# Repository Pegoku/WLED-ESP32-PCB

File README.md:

# WLED-PCB

This project is a WLED Controller designed using KiCad. The WLED-PCB is controlled using an ESP32 and can be powered via the Screw Terminals. It is capable of driving multiple RGB Strips and Neopixels. It also has a Fuse Holder per channel to protect the circuit from overcurrent.

## Schematic

## PCB Layout

## 3D View

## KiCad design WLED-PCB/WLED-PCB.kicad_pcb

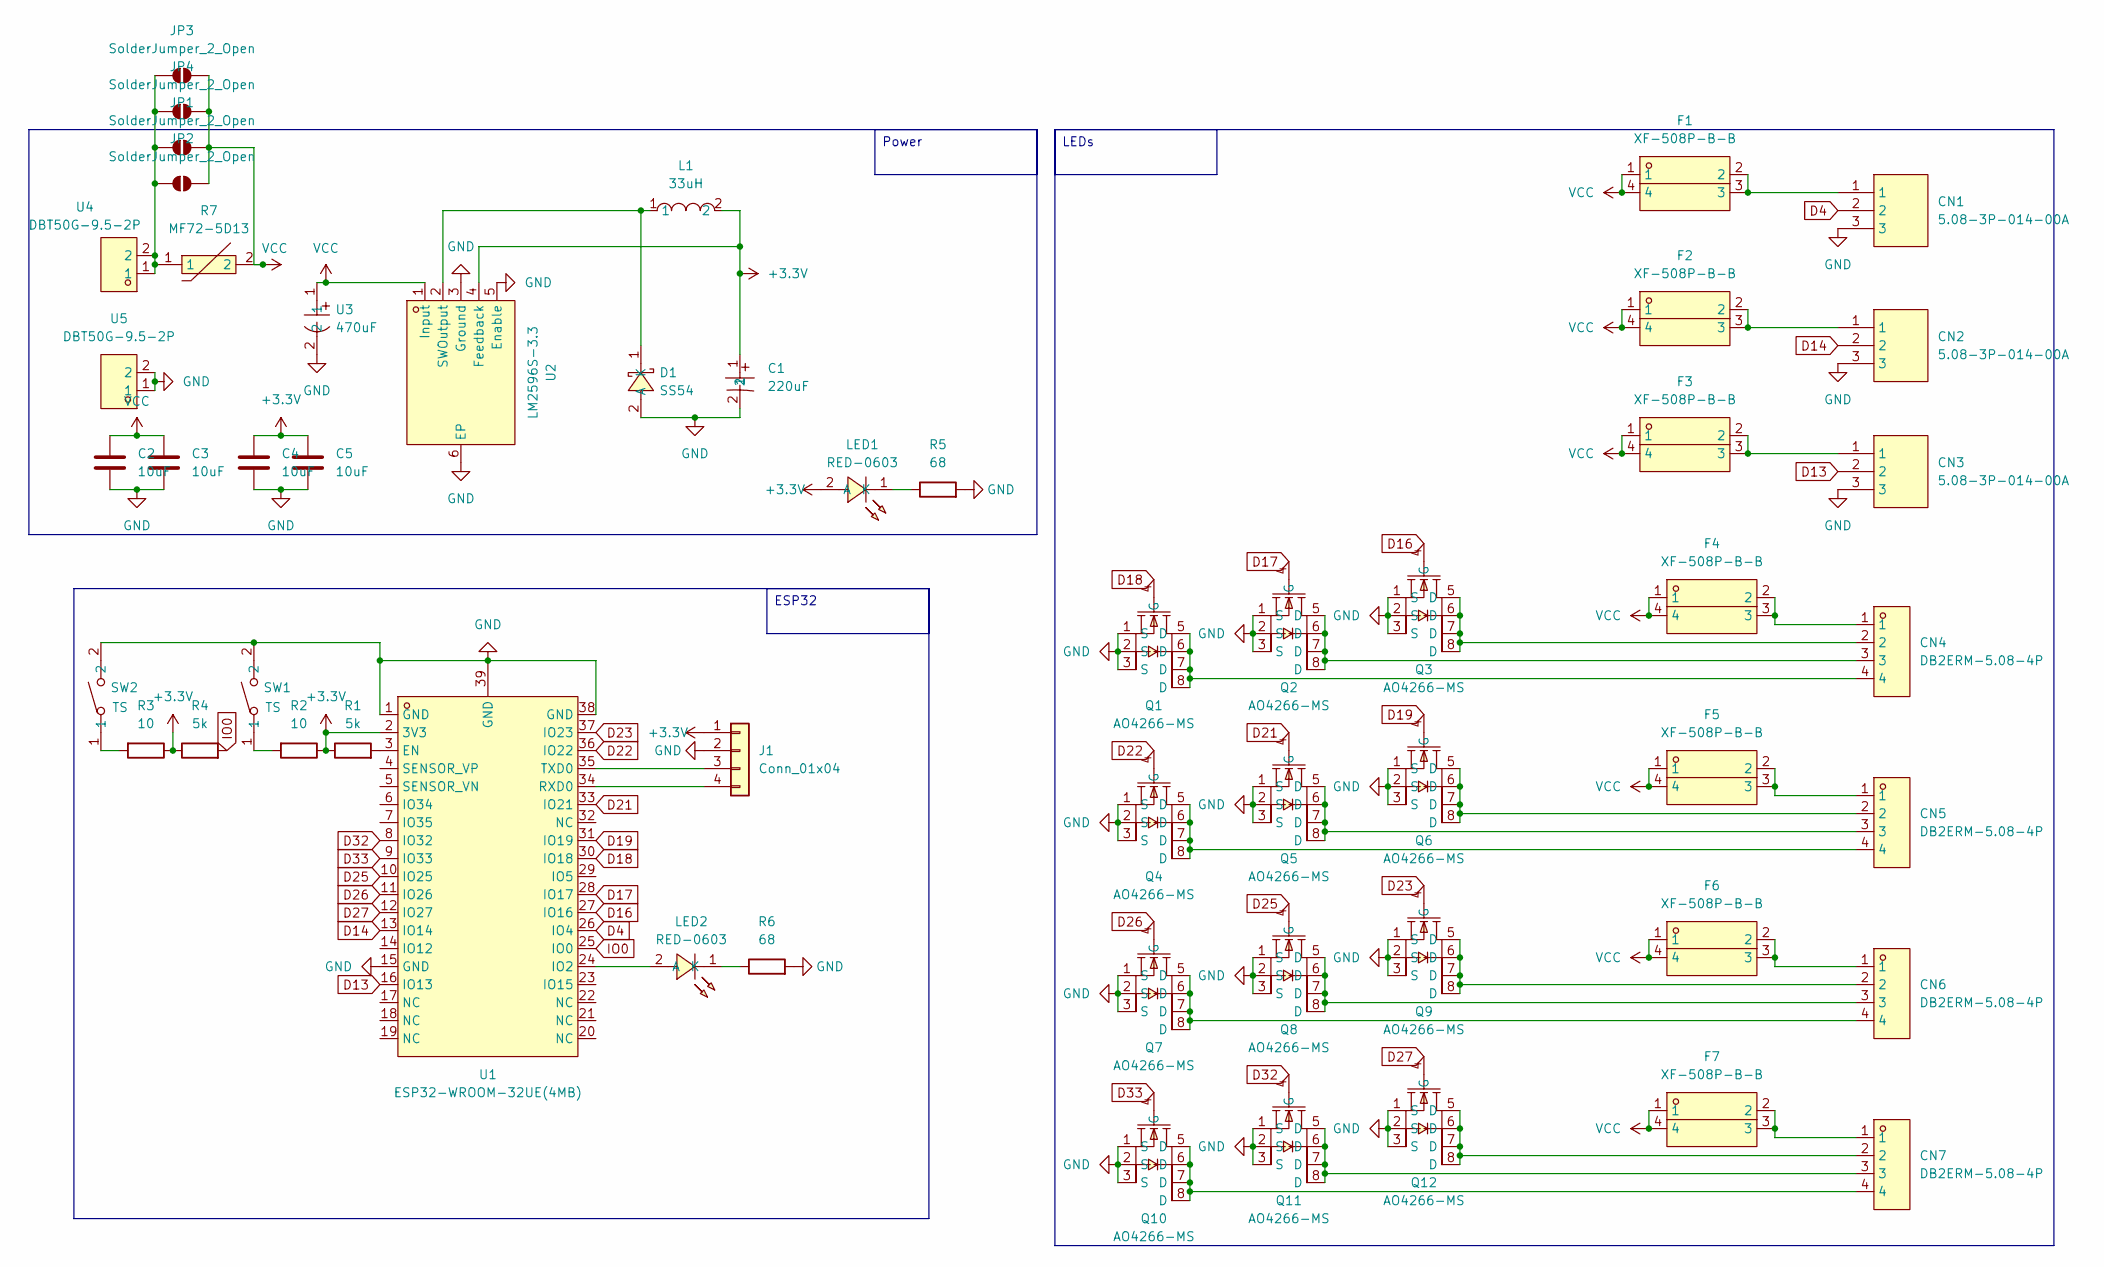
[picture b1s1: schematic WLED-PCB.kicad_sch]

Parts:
C1: 220uF; CAP-TH_BD6.3-P2.50-D1.0-FD; LCSC Part C122241
C2, C3, C4, C5: 10uF; C_1206_3216Metric_Pad1.33x1.80mm_HandSolder; LCSC C237304
CN1, CN2, CN3: 5.08-3P-014-00A; CONN-TH_WJ2EDGRM-5.08-3P; LCSC Part C49238
CN4, CN5, CN6, CN7: DB2ERM-5.08-4P; CONN-TH_4P-P5.08_DB2ERM-5.08-4P; LCSC Part C395755
D1: SS54; SMA_L4.3-W2.6-LS5.0-RD; LCSC Part C3018536
F1, F2, F3, F4, F5, F6, F7: XF-508P-B-B; FUSE-TH_4P-L16.0-W6.7; LCSC Part C19727305
J1: Conn_01x04; PinHeader_1x04_P2.54mm_Vertical
JP1, JP2, JP3, JP4: SolderJumper_2_Open; SolderJumper-2_P1.3mm_Open_TrianglePad1.0x1.5mm
L1: 33uH; IND-SMD_L7.1-W6.6_SRP6030VA; LCSC Part C22463826
LED1, LED2: RED-0603; LED0603-RD_RED; LCSC Part C965799
Q1, Q2, Q3, Q4, Q5, Q6, Q7, Q8, Q9, Q10, Q11, Q12: AO4266-MS; SOP-8_L4.9-W3.9-P1.27-LS6.0-BL; LCSC Part C3008148
R1, R4: 5k; R_0603_1608Metric_Pad0.98x0.95mm_HandSolder
R2, R3: 10; R_0603_1608Metric_Pad0.98x0.95mm_HandSolder
R5, R6: 68; R_0603_1608Metric_Pad0.98x0.95mm_HandSolder; LCSC C242566
R7: MF72-5D13; RES-TH_L15.5-W6.0-P7.50-D0.8-S5.20; LCSC Part C72683
SW1, SW2: TS; SW-SMD_L3.9-W3.0-P4.45; LCSC Part C720477
U1: ESP32-WROOM-32UE(4MB); WIFI-SMD_ESP32-WROOM-32UE; LCSC Part C701344
U2: LM2596S-3.3; TO-263-5_L10.0-W9.0-P1.70-LS15.2-BR; LCSC Part C7419978
U3: 470uF; CAP-TH_BD10.0-P5.00-D0.6-FD; LCSC Part C5438877
U4, U5: DBT50G-9.5-2P; CONN-TH_2P-P9.50_DBT50G-9.5-2P; LCSC Part C395958

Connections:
+3.3V: C1.1, C4.1, C5.1, J1.1, L1.2, LED1.2 (A), R1.1, R2.1, R3.1, R4.1, U1.2 (3V3), U2.4 (Feedback)
D4: CN1.2, U1.26 (IO4)
D13: CN3.2, U1.16 (IO13)
D14: CN2.2, U1.13 (IO14)
D16: Q3.4 (G), U1.27 (IO16)
D17: Q2.4 (G), U1.28 (IO17)
D18: Q1.4 (G), U1.30 (IO18)
D19: Q6.4 (G), U1.31 (IO19)
D21: Q5.4 (G), U1.33 (IO21)
D22: Q4.4 (G), U1.36 (IO22)
D23: Q9.4 (G), U1.37 (IO23)
D25: Q8.4 (G), U1.10 (IO25)
D26: Q7.4 (G), U1.11 (IO26)
D27: Q12.4 (G), U1.12 (IO27)
D32: Q11.4 (G), U1.8 (IO32)
D33: Q10.4 (G), U1.9 (IO33)
GND: C1.2, C2.2, C3.2, C4.2, C5.2, CN1.3, CN2.3, CN3.3, D1.2 (A), J1.2, Q1.1 (S), Q1.2 (S), Q1.3 (S), Q2.1 (S), Q2.2 (S), Q2.3 (S), Q3.1 (S), Q3.2 (S), Q3.3 (S), Q4.1 (S), Q4.2 (S), Q4.3 (S), Q5.1 (S), Q5.2 (S), Q5.3 (S), Q6.1 (S), Q6.2 (S), Q6.3 (S), Q7.1 (S), Q7.2 (S), Q7.3 (S), Q8.1 (S), Q8.2 (S), Q8.3 (S), Q9.1 (S), Q9.2 (S), Q9.3 (S), Q10.1 (S), Q10.2 (S), Q10.3 (S), Q11.1 (S), Q11.2 (S), Q11.3 (S), Q12.1 (S), Q12.2 (S), Q12.3 (S), R5.2, R6.2, SW1.2, SW2.2, U1.1 (GND), U1.15 (GND), U1.38 (GND), U1.39 (GND), U2.3 (Ground), U2.5 (Enable), U2.6 (EP), U3.2, U5.1, U5.2
IO0: R4.2, U1.25 (IO0)
unnamed: CN1.1, F1.2, F1.3
unnamed: CN2.1, F2.2, F2.3
unnamed: CN3.1, F3.2, F3.3
unnamed: CN4.1, F4.2, F4.3
unnamed: CN4.2, Q3.5 (D), Q3.6 (D), Q3.7 (D), Q3.8 (D)
unnamed: CN4.3, Q2.5 (D), Q2.6 (D), Q2.7 (D), Q2.8 (D)
unnamed: CN4.4, Q1.5 (D), Q1.6 (D), Q1.7 (D), Q1.8 (D)
unnamed: CN5.1, F5.2, F5.3
unnamed: CN5.2, Q6.5 (D), Q6.6 (D), Q6.7 (D), Q6.8 (D)
unnamed: CN5.3, Q5.5 (D), Q5.6 (D), Q5.7 (D), Q5.8 (D)
unnamed: CN5.4, Q4.5 (D), Q4.6 (D), Q4.7 (D), Q4.8 (D)
unnamed: CN6.1, F6.2, F6.3
unnamed: CN6.2, Q9.5 (D), Q9.6 (D), Q9.7 (D), Q9.8 (D)
unnamed: CN6.3, Q8.5 (D), Q8.6 (D), Q8.7 (D), Q8.8 (D)
unnamed: CN6.4, Q7.5 (D), Q7.6 (D), Q7.7 (D), Q7.8 (D)
unnamed: CN7.1, F7.2, F7.3
unnamed: CN7.2, Q12.5 (D), Q12.6 (D), Q12.7 (D), Q12.8 (D)
unnamed: CN7.3, Q11.5 (D), Q11.6 (D), Q11.7 (D), Q11.8 (D)
unnamed: CN7.4, Q10.5 (D), Q10.6 (D), Q10.7 (D), Q10.8 (D)
unnamed: D1.1 (K), L1.1, U2.2 (SWOutput)
unnamed: J1.3, U1.35 (TXD0)
unnamed: J1.4, U1.34 (RXD0)
unnamed: JP1.1 (A), JP2.1 (A), JP3.1 (A), JP4.1 (A), R7.1, U4.1, U4.2
unnamed: LED1.1 (K), R5.1
unnamed: LED2.2 (A), U1.24 (IO2)
unnamed: LED2.1 (K), R6.1
unnamed: R2.2, SW1.1
unnamed: R3.2, SW2.1
unnamed: R1.2, U1.3 (EN)
VCC: C2.1, C3.1, F1.1, F1.4, F2.1, F2.4, F3.1, F3.4, F4.1, F4.4, F5.1, F5.4, F6.1, F6.4, F7.1, F7.4, JP1.2 (B), JP2.2 (B), JP3.2 (B), JP4.2 (B), R7.2, U2.1 (Input), U3.1

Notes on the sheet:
LEDs
ESP32
Power

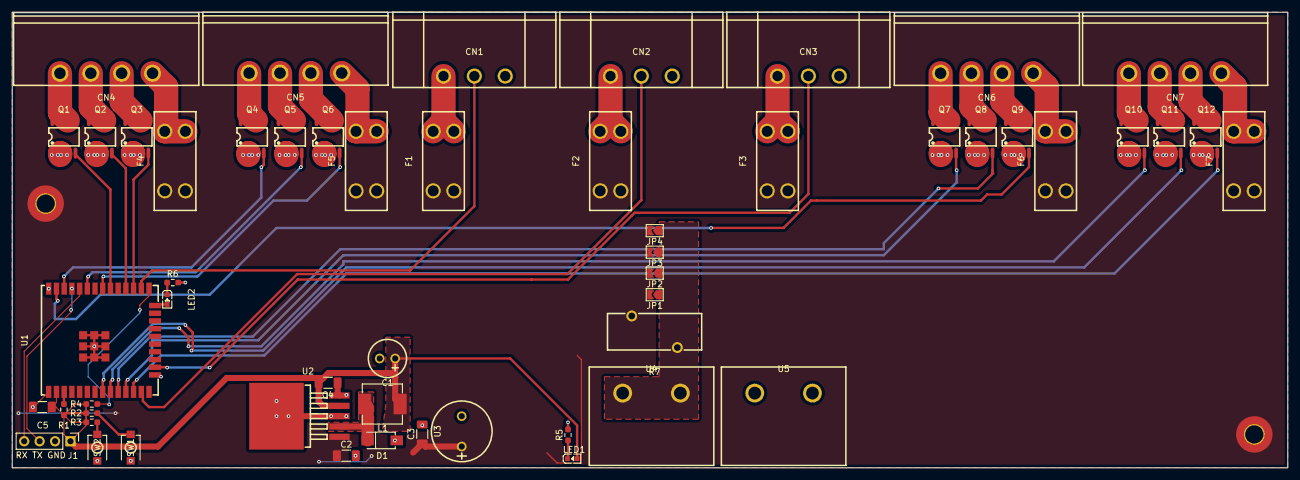
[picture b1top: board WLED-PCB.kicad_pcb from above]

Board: 2 copper layers, 210.0 x 75.0 mm, 54 parts (0 on the bottom side), 48 nets.

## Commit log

2025-02-26 finished PCB
